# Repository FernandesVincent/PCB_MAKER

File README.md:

# PCB_MAKER

Exercice du 30/01 pour le 03/02

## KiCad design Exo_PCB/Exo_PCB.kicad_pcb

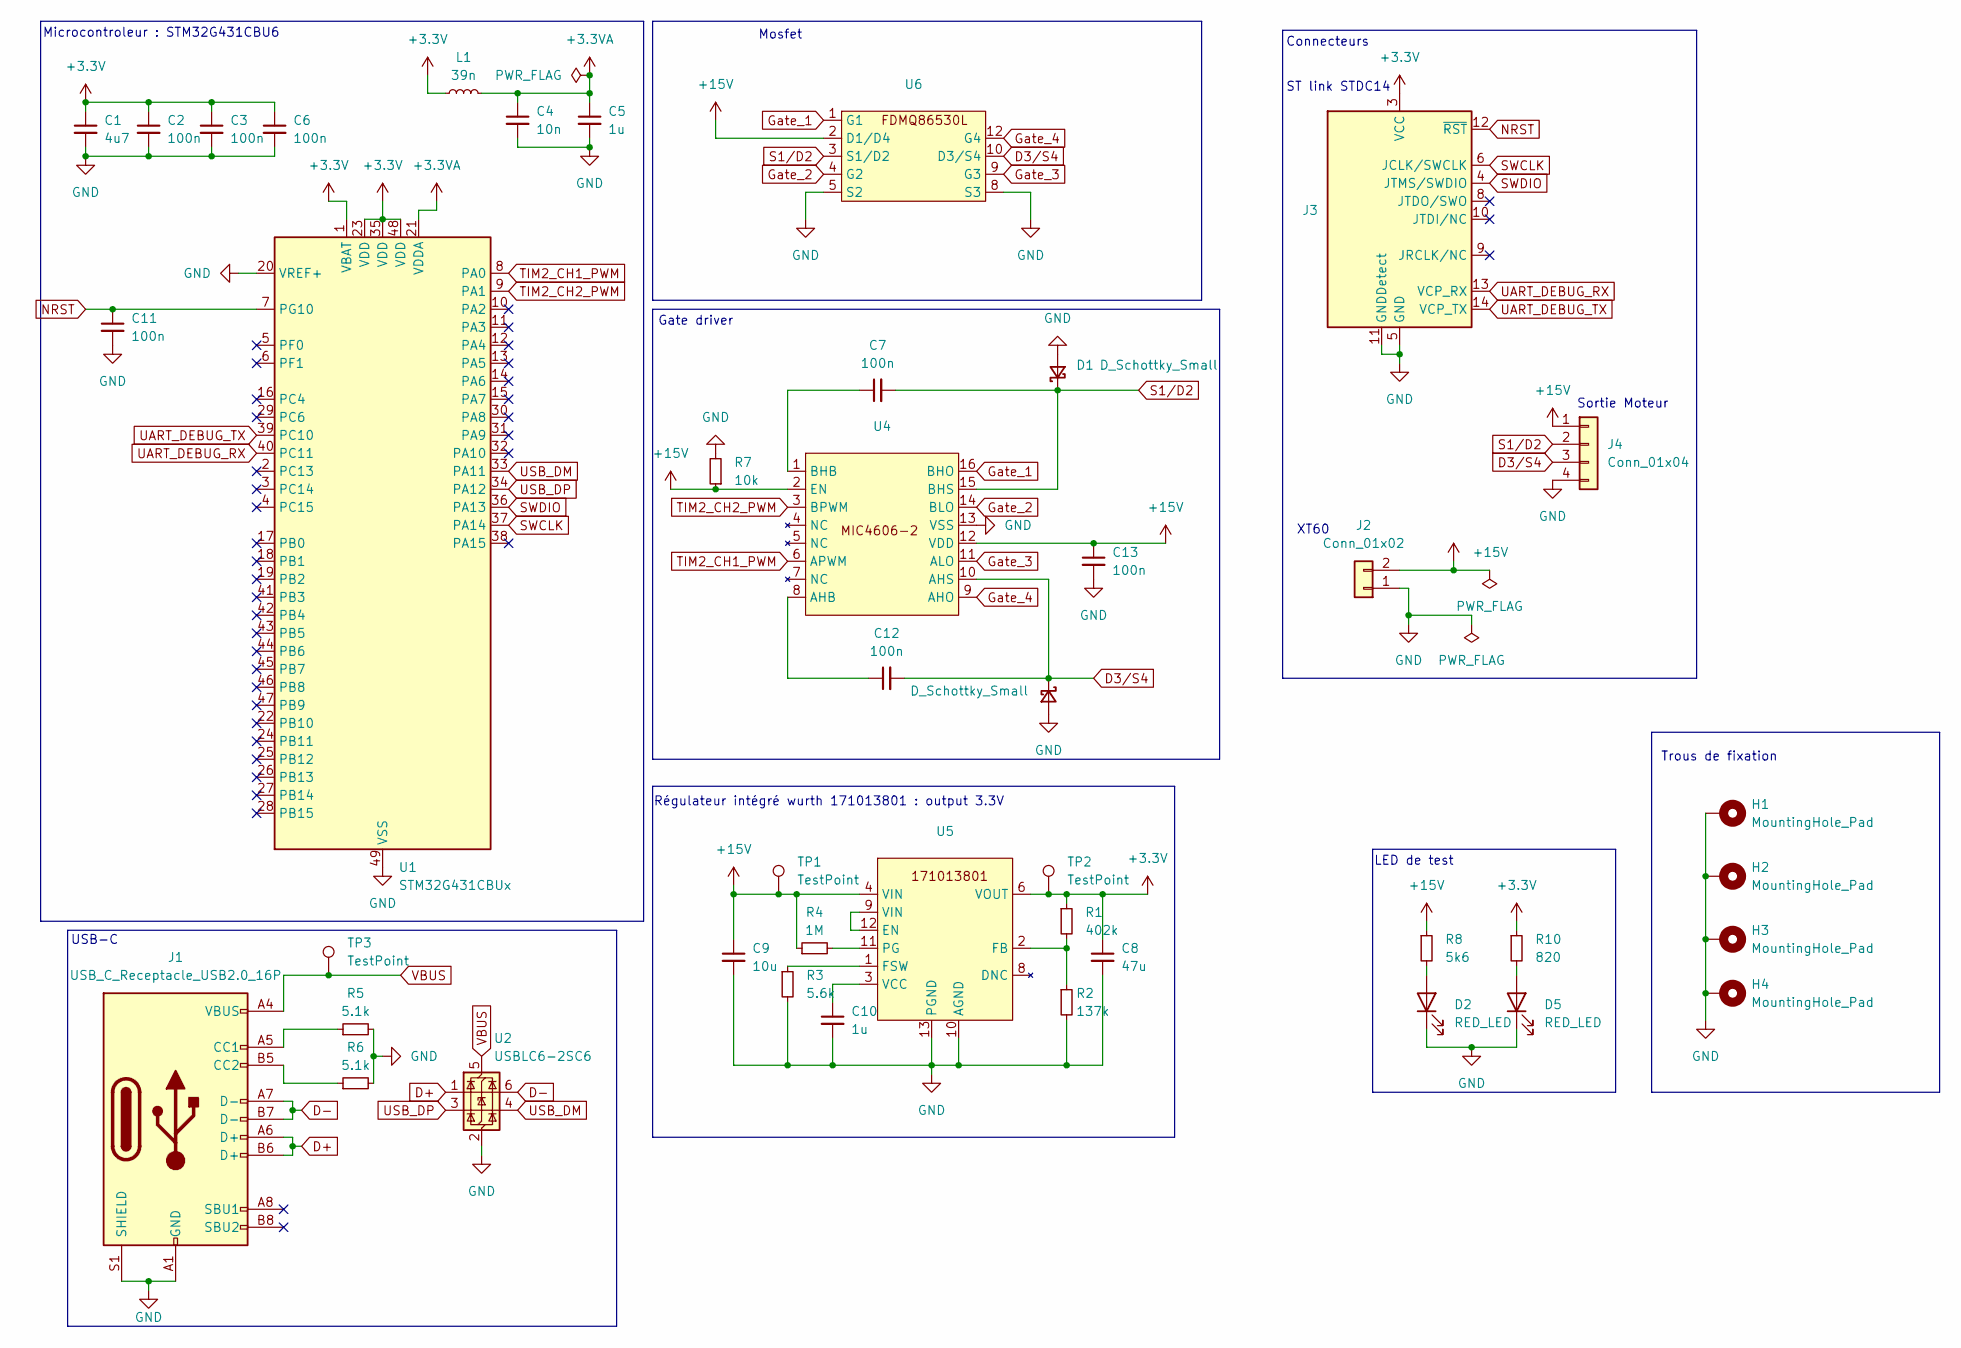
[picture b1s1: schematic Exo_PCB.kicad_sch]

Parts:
C1: 4u7; C_0402_1005Metric
C2, C3, C6, C7, C11, C12, C13: 100n; C_0402_1005Metric
C4: 10n; C_0402_1005Metric
C5, C10: 1u; C_0402_1005Metric
C8: 47u; C_0402_1005Metric
C9: 10u; C_0402_1005Metric
D1, D3: D_Schottky_Small; D_0603_1608Metric_Pad1.05x0.95mm_HandSolder
D2, D5: RED_LED; LED_0603_1608Metric; MPN 150060RS55040
H1, H2, H3, H4: MountingHole_Pad; MountingHole_3.2mm_M3_Pad_Via
J1: USB_C_Receptacle_USB2.0_16P; USB_C_Receptacle_G-Switch_GT-USB-7010ASV
J2: Conn_01x02; AMASS_XT60-M_1x02_P7.20mm_Vertical
J3: Conn_ST_STDC14; PinHeader_2x07_P1.27mm_Vertical_SMD; MPN STLINK-V3MINIE
J4: Conn_01x04; JST_EH_B4B-EH-A_1x04_P2.50mm_Vertical
L1: 39n; L_0805_2012Metric
R1: 402k; R_0402_1005Metric
R2: 137k; R_0402_1005Metric
R3: 5.6k; R_0402_1005Metric
R4: 1M; R_0402_1005Metric
R5, R6: 5.1k; R_0402_1005Metric
R7: 10k; R_0402_1005Metric
R8: 5k6; R_0402_1005Metric
R10: 820; R_0402_1005Metric
TP1, TP2, TP3: TestPoint; TestPoint_Pad_D1.5mm
U1: STM32G431CBUx; QFN-48-1EP_7x7mm_P0.5mm_EP5.6x5.6mm; MPN STM32G431CBU6
U2: USBLC6-2SC6; SOT-23-6
U4: MIC4606-2YTS-TR; MPN MIC4606-2YTS-TR
U5: 171013801; MPN 171013801
U6: FDMQ86530L; MPN FDMQ86530L

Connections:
+3.3V: C1.1, C2.1, C3.1, C6.1, C8.1, J3.3 (VCC), L1.1, R1.1, R10.1, TP2.1, U1.1 (VBAT), U1.23 (VDD), U1.35 (VDD), U1.48 (VDD), U5.6 (VOUT), U5.7 (VOUT); also elsewhere on the board
+3.3VA: C4.1, C5.1, L1.2, U1.21 (VDDA)
+15V: C9.1, C13.1, J2.2, J4.1, R4.1, R7.1, R8.1, TP1.1, U4.2 (EN), U4.12 (VDD), U5.4 (VIN), U5.5 (VIN), U6.2 (D1/D4), U6.11 (D1/D4), U6.13 (D1/D4); also elsewhere on the board
D3/S4: C12.2, D3.1 (K), J4.3, U4.10 (AHS), U6.10 (D3/S4), U6.14 (D3/S4)
D+: J1.A6 (D+), J1.B6 (D+), U2.1 (I/O1)
D-: J1.A7 (D-), J1.B7 (D-), U2.6 (I/O1)
GND: C1.2, C2.2, C3.2, C4.2, C5.2, C6.2, C8.2, C9.2, C10.2, C11.2, C13.2, D1.2 (A), D2.1 (K), D3.2 (A), D5.1 (K), H1.1, H2.1, H3.1, H4.1, J1.A1 (GND), J1.A12 (GND), J1.B1 (GND), J1.B12 (GND), J1.S1 (SHIELD), J2.1, J3.5 (GND), J3.7 (GND), J3.11 (GNDDetect), J4.4, R2.2, R3.2, R5.2, R6.2, R7.2, U1.20 (VREF+), U1.49 (VSS), U2.2 (GND), U4.13 (VSS), U5.10 (AGND), U5.13 (PGND), U6.5 (S2), U6.6 (S2), U6.7 (S3), U6.8 (S3)
Gate_1: U4.16 (BHO), U6.1 (G1)
Gate_2: U4.14 (BLO), U6.4 (G2)
Gate_3: U4.11 (ALO), U6.9 (G3)
Gate_4: U4.9 (AHO), U6.12 (G4)
NRST: C11.1, J3.12 (~RST), U1.7 (PG10)
unnamed: D2.2 (A), R8.2
unnamed: D5.2 (A), R10.2
unnamed: J1.A5 (CC1), R5.1
unnamed: J1.B5 (CC2), R6.1
unnamed: C12.1, U4.8 (AHB)
unnamed: C7.1, U4.1 (BHB)
unnamed: U5.9 (VIN), U5.12 (EN)
unnamed: R1.2, R2.1, U5.2 (FB)
unnamed: R3.1, U5.1 (FSW)
unnamed: R4.2, U5.11 (PG)
unnamed: C10.1, U5.3 (VCC)
S1/D2: C7.2, D1.1 (K), J4.2, U4.15 (BHS), U6.3 (S1/D2), U6.15 (S1/D2)
SWCLK: J3.6 (JCLK/SWCLK), U1.37 (PA14)
SWDIO: J3.4 (JTMS/SWDIO), U1.36 (PA13)
TIM2_CH1_PWM: U1.8 (PA0), U4.6 (APWM)
TIM2_CH2_PWM: U1.9 (PA1), U4.3 (BPWM)
UART_DEBUG_RX: J3.13 (VCP_RX), U1.40 (PC11)
UART_DEBUG_TX: J3.14 (VCP_TX), U1.39 (PC10)
USB_DM: U1.33 (PA11), U2.4 (I/O2)
USB_DP: U1.34 (PA12), U2.3 (I/O2)
VBUS: J1.A4 (VBUS), J1.A9 (VBUS), J1.B4 (VBUS), J1.B9 (VBUS), TP3.1, U2.5 (VBUS); also elsewhere on the board

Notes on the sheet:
USB-C
Sortie Moteur
Trous de fixation
LED de test
XT60
Régulateur intégré wurth 171013801 : output 3.3V
Connecteurs
Microcontroleur : STM32G431CBU6
Gate driver
ST link STDC14
Mosfet

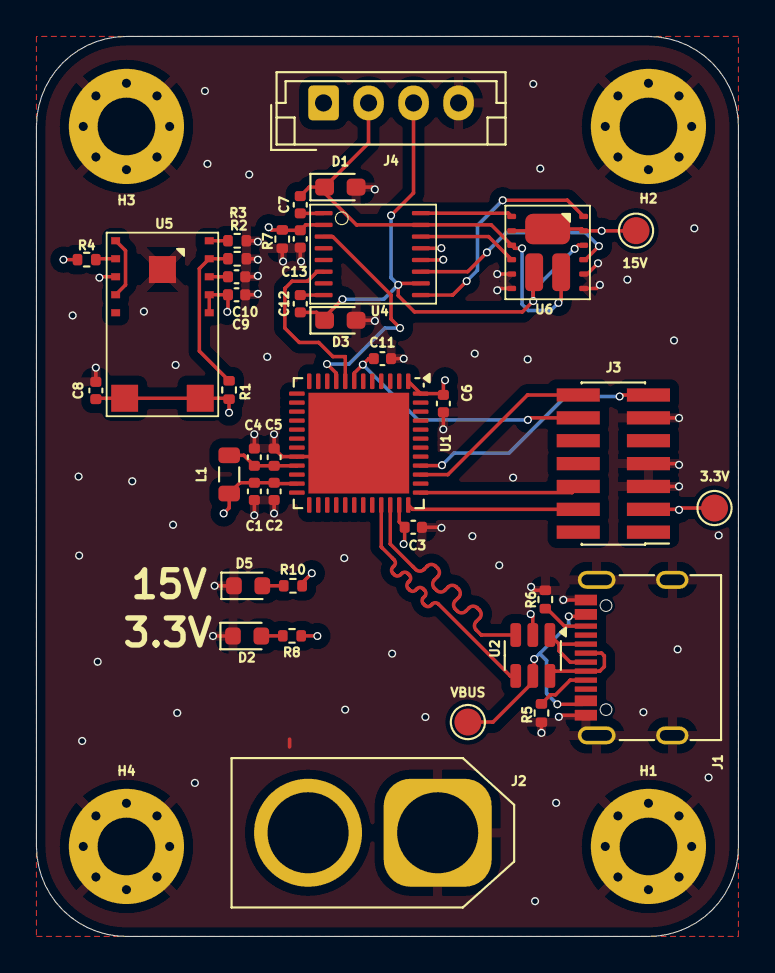
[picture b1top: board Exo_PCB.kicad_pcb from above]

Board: 4 copper layers, 39.0 x 50.0 mm, 43 parts (0 on the bottom side), 33 nets.

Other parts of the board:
3.3V, 15V: TestPoint; TestPoint_Pad_D1.5mm
VBUS: TestPoint; TestPoint_Pad_D1.5mm

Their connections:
+3.3V: 3.3V.1; also elsewhere on the board
+15V: 15V.1; also elsewhere on the board
VBUS: VBUS.1; also elsewhere on the board
